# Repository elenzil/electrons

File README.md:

# Analog LED Soft-Fade Lamp — Discussion Summary

**Discussion dates:** November 15–19, 2026  
**Project:** 5 V USB-C-powered porcelain lamp, analog soft-on/soft-off LED control  
**Current reference:** User-edited KiCad design with **eight optional LED outputs** (`lamp01_100`)

## 1. Goal and decisions

Build a compact, reliable LED circuit for a porcelain lamp that fades smoothly on and off, without PWM, a microcontroller, or an LED-driver IC. The user prefers through-hole components and external wiring to the LEDs, USB-C power module, and panel-mounted switch.

The working electrical topology is a **single IRLZ44N N-channel MOSFET** controlled by an **SPDT ON–ON toggle** and a simple RC network. The design began with three tested LED branches, was expanded in a generated KiCad draft to seven outputs, and was subsequently redesigned by the user to provide **eight outputs**. **Not all eight outputs need to be connected or used**; an unused LED branch can remain open.

Earlier, different MOSFET/switch arrangements were investigated, but the user explicitly chose to set those aside. This document describes the final single-MOSFET approach rather than the superseded experiments.

## 2. Working circuit topology

| Part or connection | Working reference configuration |
|---|---|
| Power | Nominal 5 V DC supplied by an external Adafruit HUSB238 USB-C PD breakout |
| Switching transistor | One IRLZ44N logic-level N-channel MOSFET, low-side switch |
| Control switch | External, three-terminal SPDT ON–ON toggle |
| Timing resistor | 300 kΩ between switch common and MOSFET gate |
| Timing capacitor | 10 µF from gate to ground; positive lead at gate, negative at ground |
| LED branches | Each LED has its **own** 10 Ω series resistor |
| Outputs in current KiCad design | Eight independently resistor-limited LED connection pairs |
| Control method | Analog gate charge/discharge; no PWM |

**Functional wiring:**

- One SPDT throw connects to **+5 V** (fade on); the other connects to **GND** (fade off). The switch common goes through the **300 kΩ** resistor to the MOSFET gate.
- The **10 µF** capacitor is wired between the MOSFET **gate** and **ground**.
- Each populated LED branch follows **+5 V → its own 10 Ω resistor → LED anode → LED cathode → common MOSFET drain**.
- The MOSFET **source** connects to ground. The MOSFET switches the shared LED return.
- In the intended TO-220 package, viewing the marked front with leads downward, the IRLZ44N pins are **Gate–Drain–Source** from left to right. The metal tab is connected to **Drain**, **not ground**. Verify the actual device and footprint before assembly.

The nominal gate RC time constant is **300 kΩ × 10 µF = 3 seconds**. Visible fades need not last exactly three seconds because LED light output and MOSFET conduction are nonlinear functions of gate voltage. The single-resistor arrangement provides charging and discharging through the same nominal 300 kΩ resistance.

## 3. Breadboard behavior and measurements

The **three-LED** version was tested and reported to produce satisfactory, smooth fading. The measurements below came from different tests and should **not** be treated as one simultaneous, internally balanced set of voltage readings.

| Measurement | Reported approximate result |
|---|---|
| Three-LED total current | About **0.42–0.45 A** in representative tests |
| Per-LED branch current | About **0.14–0.15 A** |
| Voltage across each 10 Ω resistor | About **1.4–1.5 V** |
| LED forward voltage | Approximately **2.7–3.05 V**, depending on test |
| USB meter voltage | Around **4.89 V** in one test |
| Breadboard rails | Around **4.6–4.8 V**, depending on wiring/test |
| MOSFET drain–source drop when fully on | Approximately **0.007 V** at roughly 0.42 A |

Breadboard and lead resistance caused measurable supply losses. Adding another jumper improved one rail by roughly **0.05 V**; other checks found losses of approximately **0.08 V** in the positive path and **0.14 V** in the ground path. These observations prompted attention to wiring resistance and power distribution in the PCB.

With **0.15 A** flowing through a **10 Ω** resistor, dissipation is **I²R = 0.225 W** per resistor. This is uncomfortably close to a typical 0.25 W component's nominal rating, particularly inside a lamp. At the same per-branch current, **eight active LEDs would draw approximately 1.2 A** in total; that is a **projection, not a tested eight-LED measurement**. Power-supply capacity, voltage drop, resistor ratings, LED heat, and MOSFET thermal performance still require full-load verification.

## 4. KiCad development and revisions

### Three-output draft (November 15)

An editable, through-hole KiCad project was generated for the working three-LED circuit. It had an approximately **60 × 42 mm** two-layer board, an external USB-C breakout and SPDT switch, individually resistor-limited off-board LEDs, and the same MOSFET/RC topology. Native KiCad ERC and DRC had **not** been run in the generation environment.

### Seven-output generated revision (November 15)

At the user's request, the design was expanded to seven LED branches, retaining a separate resistor for each. The requested mechanical and routing requirements were:

- **Four 2.5 mm non-plated mounting holes**.
- **1.5 mm copper traces on all electrical paths**, including the gate circuit.
- Through-hole parts, with LED assemblies, USB-C breakout, and switch off-board.

The generated revision used an approximately **84 × 98 mm**, two-layer PCB and a **74 × 88 mm mounting-hole center pattern**. It specified 10 Ω, **2 W** LED resistors with 18 mm lead spacing. Internal script-based topology, track-width, and clearance checks were reported as passing; **native KiCad ERC/DRC and physical fit verification remained outstanding**. The size was potentially too large for the lamp.

### User-edited eight-output design reviewed November 18–19

The user subsequently presented a more compact KiCad design, identified as **`lamp01_100`**. The user confirmed that the move to **eight** LED outputs was deliberate, and that some could remain unused. The review described:

| Property | User's compact design |
|---|---|
| LED branches | **8**: D10–D17, R10–R17, J10–J17 |
| Resistor arrangement | A separate 10 Ω resistor for each branch |
| MOSFET and fade control | Single IRLZ44N with the existing analog RC approach |
| Board dimensions | Approximately **51.5 × 39 mm** |
| Routing | **Single copper layer**, with **1.0 mm traces** |
| Mounting | Four **3.2 mm** mounting holes |
| Wire-connection drill size | Approximately **0.7 mm** |
| LED-resistor footprint | Small vertical **DIN0207**, nominally 0.25 W |

The assistant's geometric/connectivity inspection **reported all existing routed pads connected**, no apparent cross-net copper shorts, and approximately **0.4 mm** minimum clearance in that check. This was **not** a native KiCad DRC pass or a fabrication sign-off.

The smaller layout was viewed favorably, but it differs from the **earlier requested** 1.5 mm traces and 2.5 mm mounting holes. Whether those original physical specifications still apply is an open design decision; the eight-LED count itself is **not** a problem.

## 5. Issues and changes discussed for the compact PCB

1. **LED resistor power and footprints — highest concern.** The current vertical DIN0207 footprints typically correspond to ~0.25 W resistors, while one 10 Ω resistor may dissipate about 0.225 W at the measured operating current. The discussion recommended moving to **at least 1 W-rated resistors** and footprint sizes appropriate to the actual parts. Verify resistor body dimensions, orientation, spacing, and cooling.
2. **Wire terminal drill diameter.** Approximately **0.7 mm** holes may be difficult for the intended **22 AWG silicone wire**. Suggested target: roughly **1.0–1.2 mm** drill holes, with suitably larger pads and space for soldering and strain relief. Confirm final wire preparation and copper-pad geometry.
3. **Original trace-width target.** Current traces are **1.0 mm**, rather than the requested **1.5 mm**. Decide whether to restore the original rule and reroute as necessary; evaluate board-size consequences.
4. **Original mounting-hole target.** Current holes are **3.2 mm**, rather than **2.5 mm**. Confirm intended fasteners, physical edge clearance, and whether 3.2 mm is now preferred.
5. **Power and heat at higher load.** Progressively test more populated branches, supply voltage at load, wire and board temperature, LED thermal mounting, resistor temperatures, and total current. The eight-output board does **not** require eight LEDs to be installed.
6. **Fabrication verification.** Run **KiCad ERC and DRC**, verify schematic-to-PCB consistency, confirm MOSFET pinout and footprints, inspect silk and edge/drill clearances, and review Gerbers and drill files before ordering.

## 6. KiCad editor guidance covered in this discussion

- **Crossing schematic wires:** Wires can cross without electrical connection if no junction dot is present. Ending one wire on another can intentionally create a junction; verify the dot and net connectivity.
- **Wire hop-overs:** The discussion identified this as a **KiCad 10** feature and gave **File → Schematic Setup → General → Formatting → Hop-over size**, selecting a visible size instead of `None`.
- **Editing custom symbols:** Open **Tools → Symbol Editor** from the Schematic Editor, choose the symbol from its custom library, make changes, and save the library. Then use **Tools → Update Symbols from Library** in the schematic to bring existing placed instances up to date.
- **Footprints are separate:** Use the PCB **Footprint Editor** to edit physical footprints; modifying a schematic symbol does not automatically alter a footprint.

## 7. Current state and next actions (November 19; superseded by section 8)

**Current intent:** Keep the **single-MOSFET, SPDT ON–ON, 300 kΩ/10 µF** analog fade circuit. Continue with the user's compact **eight-output** KiCad design; populate or connect only the LED branches needed for the porcelain lamp.

**Established:** The three-LED breadboard version worked satisfactorily, and preliminary custom geometric checks of the uploaded compact PCB did not reveal obvious short circuits or disconnected routed pads.

**Not established:** Operation, thermal performance, or current at eight LEDs; exact physical suitability of the new resistor and wire footprints; native KiCad ERC/DRC cleanliness; or PCB fabrication readiness.

**Recommended immediate sequence:** Replace/verify resistor footprints and ratings; review wire terminal drills; decide whether the initial trace/mounting-hole dimensions still apply; run native KiCad schematic and board checks; inspect fabrication outputs; and bench-test incrementally from one LED upward.

## 8. Status (as of November 20, 2026): everything ordered

The board, the LEDs and the Mouser components are all on order. Next step is bring-up when they arrive (about a week).

### Board as ordered (`lamp01_100`, OSH Park standard 2-layer, 3 boards)

- **Size and layers:** 67.5 × 31.1 mm, 2 layers, rounded corners, four 3.2 mm (M3) mounting holes.
- **Circuit:** unchanged. Single IRLZ44N MOSFET, SPDT ON–ON switch (off-board, via J2), 300 kΩ / 10 µF fade network, 8 LED outputs (J10–J17), each with its own resistor.
- **LED resistors R10–R17:** Vishay PR01 1 W metal film. It has the same slim 0207 body as a ¼ W part, so the original footprints fit.
- **Wire pads:**
  - J10–J17 and J2: 1.15 mm holes, for 22 AWG silicone wire.
  - J1: 2.15 mm holes, unchanged. Now a backup power input.
- **Power input:** on-board USB-C jack J18 (GCT USB4085-GF-A, through-hole, left edge). R2/R3 (5.1 kΩ) on CC1/CC2 make chargers supply 5 V. The HUSB238 module is no longer needed.
  - The charger must offer at least 1.5 A at 5 V.
- **Traces:** 1.5 mm for main power, necking to 0.5 mm at the jack pins.
- **Clearance:** board minimum lowered to 0.15 mm for the jack's pin pitch. OSH Park accepted it.
- **Logos:** gold (exposed copper) unicorn logos on the front and back. The footprint library is `logos.pretty`, and `logos/make_logo.py` regenerates it at any size.
- **Checks:** ERC, DRC and schematic parity are clean apart from 2 cosmetic silkscreen-at-edge warnings at the jack.
- **Fabrication:** OSH Park parsed the `.kicad_pcb` directly and detected the jack's plated slots.

### Orders

- **PCB:** OSH Park, 3 boards. Snapshot images are in `lamp01/orders/20261120/`.
- **Components:** Mouser, per `lamp01/orders/20261120/mouser_bom.xlsx`:
  - PR01 1 W resistors at 10 / 12 / 13 / 15 / 20 Ω
  - 5.1 kΩ and 300 kΩ resistors
  - C1 capacitors at 4.7 / 10 / 22 / 47 µF, for different fade speeds
  - USB4085 jacks
  - E-Switch 100SP1T1B1M1QEH toggles
- **LEDs:** LuxeonStar, 2 × **SW-08-T1** (4 × LUXEON Rebel Plus each, 2700 K, CRI 80), "No Connectors", plus LXT-SR08-12 thermal tape.
  - Each module has separate anode and cathode pads for D1–D4, so it works with the per-LED resistors.
- **Ordering lessons:** see `lamp01/orders/NOTES.md`.

### Bring-up plan

1. Fit **13 Ω** for R10–R17. With the Rebel Plus at about 2.75 V, that gives about 170 mA per LED and about 0.37 W per resistor.
   - The 2.75 V is an estimate. Check it against the voltage-vs-current curve in datasheet DS107.
2. Solder and test **one LED** first. About 2.2 V across its 13 Ω resistor means about 170 mA.
3. Add LEDs one at a time. Each time, measure the board's supply voltage, the total current and the temperatures.
   - Use 12 Ω for brighter, or 15 / 20 Ω for dimmer.
4. **Wiring:**
   - On each module, join the 4 cathodes into one return wire. The return goes to any J10–J17 pin 2; they're all the shared MOSFET drain.
   - The 4 anodes go to separate outputs.
5. Mount the modules on aluminum with the thermal tape before running them for long periods. Each module makes about 2 W of heat.
6. Try other C1 values if you want a different fade speed. The time constant is 300 kΩ × C1: about 1.4 s at 4.7 µF, 3 s at 10 µF, 6.6 s at 22 µF and 14 s at 47 µF.

### Open

- [ ] Bring-up and full-load test in the lamp: current, voltage drop, resistor and LED temperatures.
- [ ] Mounting hardware and LED heat-sinking inside the porcelain.
- [ ] Regenerate `lamp01_100.ply` / `.stl` if they're needed for the enclosure. They predate the USB-C jack and the wider board.

---

*This is a discussion and design-decision summary, not a substitute for a checked schematic, electrical testing, or a fabrication review. It intentionally excludes packaged project files, board images, and other artifacts.*

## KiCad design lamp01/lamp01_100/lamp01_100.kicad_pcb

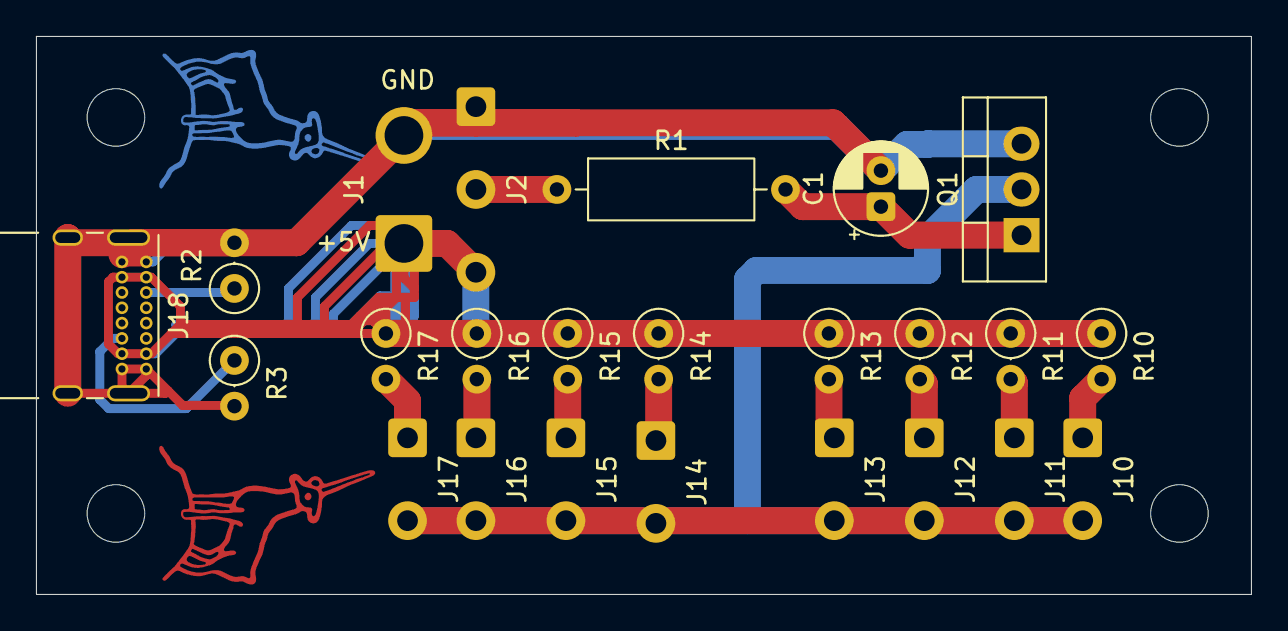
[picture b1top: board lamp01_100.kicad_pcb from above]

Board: 2 copper layers, 67.5 x 31.0 mm, 30 parts (1 on the bottom side), 15 nets.

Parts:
C1: 10uF; CP_Radial_D5.0mm_P2.00mm
H1, H2, H3, H4: MountingHole; MountingHole_3.2mm_M3
J1: Conn_01x02_Pin; SolderWire-1.5sqmm_1x02_P6mm_D1.7mm_OD3mm
J2: Conn_01x03_Pin; SolderWire-0.5sqmm_1x03_P4.6mm_D0.9mm_OD2.1mm
J10, J11, J12, J13, J14, J15, J16, J17: Conn_01x02_Pin; SolderWire-0.5sqmm_1x02_P4.6mm_D0.9mm_OD2.1mm
J18: USB4085-GF-A; USB_C_Receptacle_GCT_USB4085
Q1: IRLZ44N; TO-220-3_Vertical
R1: 300kΩ; R_Axial_DIN0309_L9.0mm_D3.2mm_P12.70mm_Horizontal
R2, R3: 5.1k; R_Axial_DIN0207_L6.3mm_D2.5mm_P2.54mm_Vertical
R10, R11, R12, R13, R14, R15, R16, R17: 10R; R_Axial_DIN0207_L6.3mm_D2.5mm_P2.54mm_Vertical
eunace1, eunace2: eunicorn_gold_12mm

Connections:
+5V: J1.1, J2.3, J18.A4 (VBUS), J18.A9 (VBUS), J18.B4 (VBUS), J18.B9 (VBUS), R10.1, R11.1, R12.1, R13.1, R14.1, R15.1, R16.1, R17.1
GND: C1.2, J1.2, J2.1, J18.A1 (GND), J18.A12 (GND), J18.B1 (GND), J18.B12 (GND), J18.SH (SHIELD), Q1.3 (S), R2.2, R3.2
unnamed: J2.2, R1.1
unnamed: J10.1, R10.2
unnamed: J10.2, J11.2, J12.2, J13.2, J14.2, J15.2, J16.2, J17.2, Q1.2 (D)
unnamed: J11.1, R11.2
unnamed: J12.1, R12.2
unnamed: J13.1, R13.2
unnamed: J14.1, R14.2
unnamed: J15.1, R15.2
unnamed: J16.1, R16.2
unnamed: J17.1, R17.2
unnamed: J18.A5 (CC1), R2.1
unnamed: J18.B5 (CC2), R3.1
unnamed: C1.1, Q1.1 (G), R1.2
